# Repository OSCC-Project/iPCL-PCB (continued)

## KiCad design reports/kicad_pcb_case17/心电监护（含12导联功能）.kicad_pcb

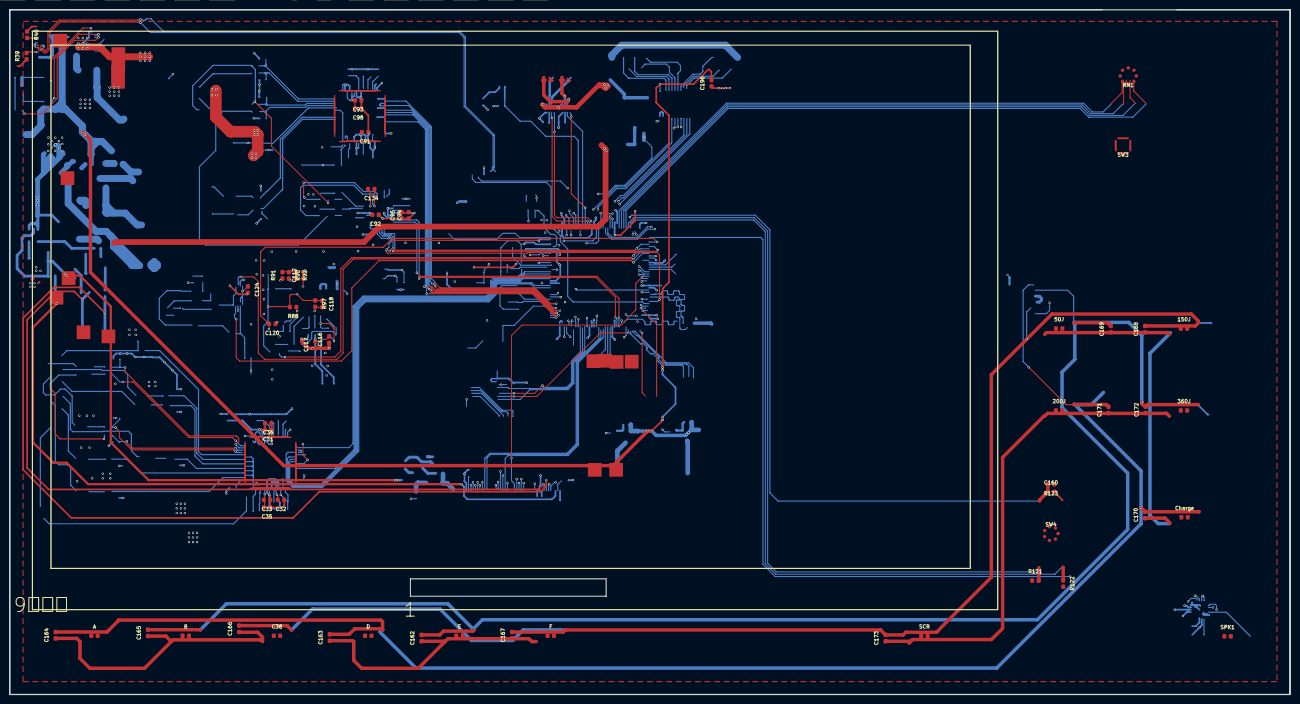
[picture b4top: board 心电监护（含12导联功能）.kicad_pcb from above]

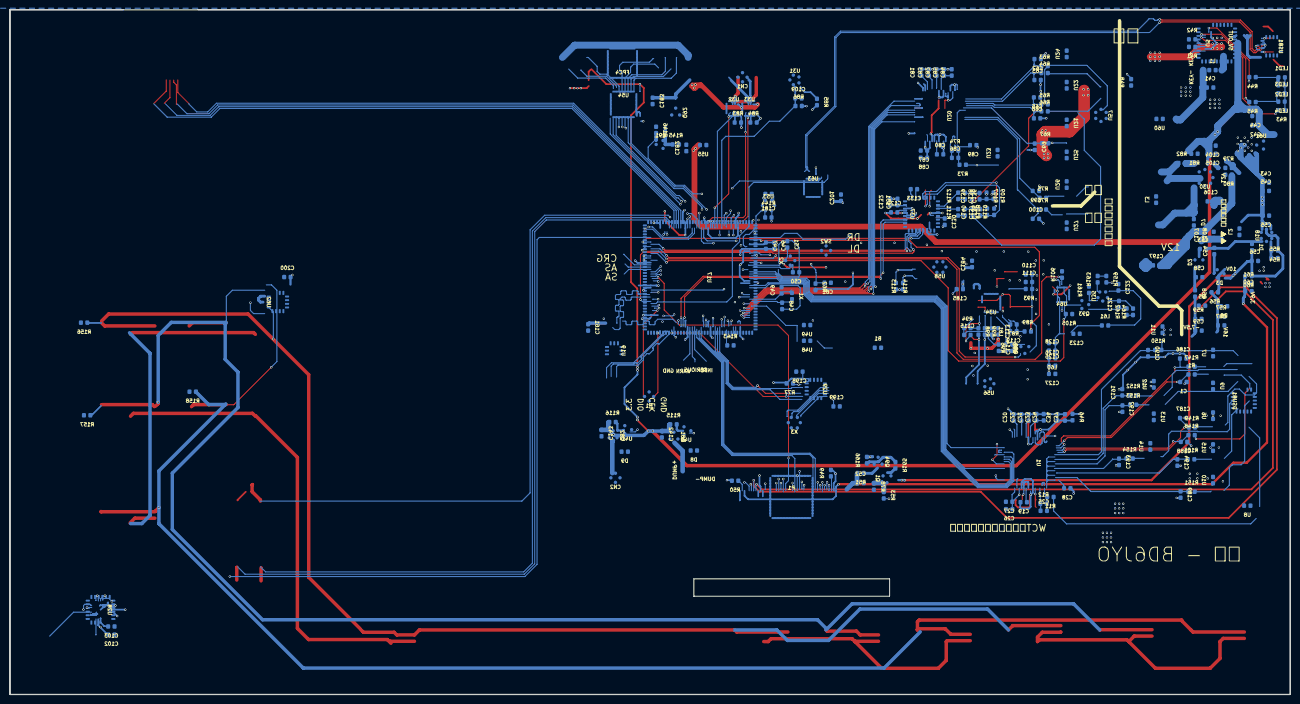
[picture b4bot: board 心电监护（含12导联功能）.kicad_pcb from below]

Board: 4 copper layers, 280.0 x 149.7 mm, 347 parts (289 on the bottom side), 274 nets.

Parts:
3.9V, 5V_OUT, 10V, 12V, 16V: test-point-0.5mm
50J, 150J, 200J, 360J: a5368f86a25146068be2408b3668e740
-7.5V: test-point-0.5mm
A: a5368f86a25146068be2408b3668e740
B: a5368f86a25146068be2408b3668e740
B1: 4e590728481542f894c6a4870e128ca6
C1, C19, C20, C21, C22, C23, C24, C25, C26, C27, C28, C31, C32, C33, C34, C35, C36, C37, C42, C43, C44, C45, C46, C47, C48, C49, C50, C51, C52, C53, C54, C55, C56, C57, C58, C59, C60, C61, C62, C63, C65, C66, C69, C80, C81, C82, C83, C84, C85, C86, C87, C88, C89, C91, C92, C93, C94, C95, C98, C99, C100, C102, C103, C104, C105, C106, C107, C108, C109, C110, C111, C112, C113, C114, C115, C116, C117, C118, C119, C120, C121, C122, C124, C125, C126, C127, C128, C129, C130, C131, C132, C133, C134, C135, C136, C137, C138, C139, C140, C142, C143, C160, C161, C162, C163, C164, C165, C166, C167, C168, C169, C170, C171, C172, C173, C181, C182, C183, C184, C185, C186, C187, C188, C189, C190, C191, C192, C193, C194, C196, C198, C199, C200, C201: b7945a7e5b5c4a0aa7293b7f08fbaef7
C38: a5368f86a25146068be2408b3668e740
C41: 0e92c3d665db49bfb035b3a293e8a128
C123: ba47d43f92bb44e8b675b656d21041e6
C197: 6b21cd17fdb1462b875b850f8c1df456
CN1: 31d9f30041aa4ccb86dff98b6131f5a0
CN2: b02f860fd06041c4a03dff9e4e9a9d56
Charge: a5368f86a25146068be2408b3668e740
D: a5368f86a25146068be2408b3668e740
D1: 4b7626d9e3dc4ab4b1f5a40703e7ad59
D2, D3: 9c46af5127664003a46938238bb95ce1
D5, D6: 91ac8cb66aa04e808b69908295fe52e9
D7: 4c0e46bca29c4c6b81e5bf8c40af5be7
D8, D9: 5d0c16af079e42cfb253586e56d88736
DSUB1: 39b3793dbb04477d8bb42acea19422e9
DUMP+: test-point-0.5mm
DUMP-: test-point-0.5mm
E: a5368f86a25146068be2408b3668e740
F: a5368f86a25146068be2408b3668e740
FPC4: cb7d1c6156c34550a72fbf6a566a445a
GND: test-point-0.5mm
H1: 73f75bc231734ab9b4af43c31c29b39a
INFO: test-point-0.5mm
KEY+: test-point-0.5mm
KEY-: test-point-0.5mm
L1, L2: 1c23e037bce9498e9d951e8e681f1670
L3: 7a41cdcb27974877a56d5e23ab1ec39c
L60, L61, L81: 870cf3ad3e8f4b4481cadf8c89e3570a
LED1, LED2: 8b6564fdb2984d8197e865d045b8fe55
LED3: 65519d43b7064742813920c87ef6d4bf
LED4: 598762258a40444a8d3e6d632ccb337f
P1: a40cf0907b584343b00a4ee89c43669f
Q1, Q94: 470d97b0775b4d198ab0a74007893075
Q80, Q91, Q93: 8f0cd7aa9b764cbb80294a6c3e96d042
Q81, Q82: 9c46af5127664003a46938238bb95ce1
Q92: 68f6e82e2aea405c86c92c228f40702a
R1, R11, R12, R39, R40, R41, R42, R43, R44, R45, R46, R48, R49, R50, R51, R53, R54, R55, R56, R57, R58, R59, R60, R61, R62, R63, R64, R65, R66, R67, R73, R74, R75, R76, R77, R78, R79, R80, R82, R83, R84, R85, R86, R107, R108, R109, R110, R111, R112, R115, R116, R121, R122, R123, R143, R144, R145, R146, R147, R148, R149, R150, R151, R152, R153, R154, R155, R156, R157, R158, R159, R161, R162, R163, R164, R165, R166: 6f4aec6b1ebd449284c4ed49b9f19c31
R81: 2640120e0c76485ea60f8241144970ee
R87, R88, R89, R90, R91, R92, R93, R94, R95, R96, R97, R98, R99, R105, R106, R113, R114: 72e69c7603aa4edf8d29985f96c3ffe3
RN1: f1a74709e41b44a49574d699140b981f
SCR: a5368f86a25146068be2408b3668e740
SERIOUS: test-point-0.5mm
SPK1: 1b99ed72e9ac48ff8cb342a8ca9438c6
SW2: d0581e74fb914419ae2671adb5a968e7
SW3: 61bb987df6594ec6aa08c5dfcf8cee7c
SW4: 5f2b1aeb4a7d44ef8f491db563029554
U1, U20: TQFP-64_L10.0-W10.0-P0.50-LS12.0-BL
U5: cda39a85f97f41da830f81e8102de607
U6, U7, U8, U9, U10, U11, U12, U13, U14, U15, U21, U22, U23, U24, U25, U26, U27: 3f067aeec7c64175b2af7de4432b0669
U17: 89ed9195d4da4ada9931ee24c9e82a56
U18: e26b29af5d3f47a2965616f8d64ee69f
U19: a692673a5b344db89108dd844333f42a
U28: 8c9603684b3541058d95c2816666bebf
U29: d974324436f24b31814a4f8fc4d5b4bf
U30: 13cf52a2d9d9472bb05fe23fd8a69656
U31: 0a26765eeea44677acb247cc684c720b
U32, U33: 6d84bfecd9c94e88953123fda0afa9f7
U34: c5b33378315045b09780d9a8558cf4a4
U35: 29113d248a374adb80ce29dd50db5bf2
U37: 27372514ed45449388039cdfe96d8606
U40, U41: 834b13ce004b4490974a88d7843f761e
U48, U49: 7f0149cf019141c4833b5e4a4083405b
U53: de513661803b4037b6dc43a570e5daf4
U54: 0a84c70d30504cdcbd1cdec5ae9f3825
U55: 878b8447bdf04bb5be66ff489c0c8653
U56: 182b4934e41a48109336b9ae788470fd
U57: 2ca98667745e4fdd9b327ad6b16e81a0
U58: e3607cc16cd8417c834685cb4e5d04ee
U60: 4159cb5bb8b246f8baa1c9276ab41b4d
U61: e27e0761c1574ba7a62473e696934099
U62: 1df479a9ca484c11abf2842f7ab43469
U63: dc02eda9a70e418f8f8ba1b589faf7b3
U64: 97c68005ac344068b28a0831b9720797
USB1: b8c1298db2324bd1a6e1152626922f4e
WARN: test-point-0.5mm
X1: 277eb1032c754119a9ed39082baf9071
X2: dfcdc5bc787d42879911d09280935ab4
X3: f82ad2619099490298d985a7bf518193

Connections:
3.3V: C26.2, C27.2, C43.2, C45.2, C55.1, C87.2, C88.2, C125.2, C127.1, C161.2, C184.2, C198.2, C199.2, C200.1, C201.2, H1.1, L2.2, L60.1, P1.12, P1.44, R46.2, R49.1, R50.1, R62.1, R77.1, R83.1, R84.1, R85.1, R86.1, R107.2, R108.1, R113.2, R114.1, R121.1, R122.2, R123.1, RN1.1, RN1.2, RN1.3, RN1.4, U1.48, U1.50, U1.52, U17.17, U17.30, U17.39, U17.52, U17.62, U17.72, U17.84, U17.95, U17.108, U17.121, U17.131, U17.143, U17.144, U18.4, U18.6, U19.8, U20.48, U20.50, U20.52, U28.4, U29.1, U29.9, U29.10, U32.8, U33.8, U37.14, U37.23, U49.2, U54.23, U54.24, U58.2, U61.2, U62.14, U63.4, U63.16
3V3SGM: C123.1, C124.1, C126.2, C128.1, L60.2, L61.2, U64.1, U64.2, U64.10
5V: U5.23, U5.24, USB1.2, USB1.11
5V_OUT: 5V_OUT.1, C42.2, C44.2, C102.1, C104.1, C105.1, C142.2, C143.2, C196.2, FPC4.9, Q81.2, Q82.2, R81.1, R115.2, R116.2, U5.19, U5.20, U5.21, U5.22, U28.17, U30.6, U54.1, U61.3
12V: 12V.1, C107.1, C108.1, C182.1, C197.1, D7.1, Q92.3, R80.2, R145.1, U55.1
12VP: C183.2, FPC4.1, FPC4.2, FPC4.3, FPC4.4, FPC4.26, FPC4.27, FPC4.28, Q92.2, U32.1, U33.1
$1N2542: C28.1, U1.1, U1.3, U1.5, U1.7, U1.9, U1.11, U1.64
$1N3912: C19.2, U1.55
$1N6305: C25.1, R11.1, R12.1, U1.62, U1.63
$2N198: R39.2, USB1.4
$2N200: R40.2, USB1.10
$2N826: R41.2, U5.6
$2N1088: R42.1, U5.5
$2N1140: L1.2, U5.14, U5.15, U5.16, U5.17, U5.18
$2N1172: C41.2, L1.1, U5.9, U60.2
$2N1635: LED1.1, LED2.2, LED3.1, LED4.2, R43.2
$2N1654: LED1.2, LED2.1, R44.2
$2N1670: LED3.2, LED4.1, R45.2
$2N4501: C53.1, C54.1, D1.2, L2.1, U18.1
$2N4625: C54.2, D3.3
$2N4652: C53.2, D2.3
$2N4895: D3.2, R56.2
$2N5230: C58.2, D2.1, R58.2
$2N9177: KEY+.1, U5.8
$2N10612: R79.2, R80.1, U30.5
$2N10742: R82.1, U30.8
$2N10757: L3.1, R81.2, R82.2, U30.7
$2N10979: D7.2, L3.2, U30.1
$2N18236: C106.2, U30.3
$3N2281: C49.2, U17.9, X1.2
$3N2284: C48.2, U17.8, X1.1
$3N2377: C50.1, U17.23, X2.3
$3N2471: C51.1, U17.24, X2.1
$3N4920: P1.43, R49.2
$3N4978: P1.4, R50.2
$3N8713: SPK1.1, U28.16
$3N8719: SPK1.2, U28.14
$3N9090: C103.1, U28.18
$3N10389: Q1.1, R53.2, R78.2
$3N12468: R83.2, U32.7
$3N12589: R84.2, U33.7
$3N19253: U17.6, U48.1, U49.1
$3N38319: R85.2, U31.1
$3N43045: R144.2, U53.3
$3N43809: Q91.3, Q92.1, R145.2
$3N86409: Q1.3, R165.1
$3N86567: Q94.1, R165.2, R166.2
$3N86579: Q94.3, R51.2
$4N2284: C89.1, U20.11, U20.64
$4N2324: C80.2, U20.55
$4N2370: C86.1, R73.1, R74.1, U20.62, U20.63
$4N6569: U34.13, U34.14
$4N6571: R93.1, U34.8
$4N6575: C112.1, R92.2, U34.10
$4N6576: R90.1, R91.2, R92.1
$4N6579: C113.2, L81.2, U34.4
$4N6582: C115.1, R94.1, R98.2, U34.2
$4N6583: C114.2, C115.2, R94.2, U34.1
$4N6584: C114.1, R95.1, R96.2
$4N6585: R95.2, U34.5
$4N6586: Q80.3, R96.1
$4N6596: C118.2, R97.2, R99.2, U34.3
$4N6599: C119.1, R87.1, R88.1, U34.6
$4N6602: C119.2, R87.2, R89.2, U34.7
$4N7474: R159.2, R163.1
$4N7475: C122.1, L61.1, U35.5
$4N7479: R162.2, R164.2
$4N7480: C121.1, R164.1, U35.4
$4N7481: C121.2, Q93.1, R162.1
$4N7483: Q93.3, U64.5, U64.7
$4N7496: R163.2, U35.1
$4N7497: Q93.2, R161.2, U35.3
$4N12574: C130.2, U37.27
$4N12606: C129.1, U37.11
$4N12858: C134.2, U37.1
$4N12860: C133.2, U37.7
$4N12864: C134.1, U37.2
$4N12868: C133.1, U37.8
$4N13059: C137.2, R108.2, R110.2, U37.3
$4N13071: C138.2, R107.1, R109.1, U37.4
$4N13252: C135.2, C137.1, C140.1
$4N13256: C136.2, C138.1, C139.1
$4N13314: C135.1, R111.2
$4N13340: C136.1, R112.2
$4N14062: Q81.1, R115.1, U40.3
$4N14471: Q82.1, R116.1, U41.3
$4N14495: D8.1, DUMP+.1, Q81.3
$4N14511: CN2.1, D9.1, Q82.3
$6N33304: U62.3, U62.4
A3.3: C31.2, C32.2, C33.2, C34.2, C35.2, C36.2, C37.2, C46.2, C47.2, C91.2, C92.2, C93.2, C94.2, C95.2, C98.2, C185.2, L81.1, R46.1, R90.2, R144.1, U1.19, U1.21, U1.22, U1.54, U1.56, U1.59, U17.33, U20.19, U20.21, U20.22, U20.54, U20.56, U20.59, U28.2, U37.12, U37.28, U37.29, U53.4, U58.1
ADC_REF3.3: C181.2, U17.32, U53.5, U53.6
AGND: C1.2, C19.1, C20.1, C21.1, C22.1, C23.1, C24.1, C28.2, C31.1, C32.1, C33.1, C34.1, C35.1, C36.1, C37.1, C46.1, C47.1, C62.2, C63.1, C65.2, C66.1, C69.1, C80.1, C81.1, C82.1, C83.1, C84.1, C85.1, C89.2, C91.1, C92.1, C93.1, C94.1, C95.1, C98.1, C99.2, C100.1, C129.2, C130.1, C131.1, C132.1, C181.1, C185.1, C186.1, C187.1, C188.2, C189.1, C190.1, C191.1, C192.1, C193.1, C194.1, R48.1, R109.2, R110.1, U1.17, U1.18, U1.20, U1.23, U1.25, U1.32, U1.53, U1.57, U1.58, U17.31, U20.17, U20.18, U20.20, U20.23, U20.25, U20.32, U20.53, U20.57, U20.58, U28.3, U37.10, U37.13, U53.1, U53.2
C1: DSUB1.12, R151.1, U10.2
C2: DSUB1.1, R150.1, U11.2
C3: DSUB1.2, R152.1, U12.2
C4: DSUB1.3, R153.1, U13.2
C5: DSUB1.4, R154.1, U14.2
C6: DSUB1.5, R155.1, U15.2
C_SA: R121.2, SW4.A, U17.67
C_SB: R122.1, SW4.B, U17.68
D+: U63.5, USB1.6, USB1.8
D-: U63.6, USB1.5, USB1.7
ECG_CLK: U1.40, U17.19
ECG_CS: U1.39, U17.18
ECG_MISO: U1.43, U17.20
ECG_MOSI: U1.34, U17.21
ECG_RESET: U1.35, U1.36, U17.14
ECG_START: U1.38, U17.15
FB: R54.1, R55.2, U18.3
GND: B1.1, C26.1, C27.1, C41.1, C42.1, C43.1, C44.1, C45.1, C48.1, C49.1, C50.2, C51.2, C52.1, C55.2, C56.1, C57.1, C58.1, C59.1, C60.1, C61.2, C87.1, C88.1, C102.2, C103.2, C104.2, C105.2, C106.1, C107.2, C108.2, C109.1, C110.2, C111.2, C112.2, C113.1, C116.1, C117.1, C120.1, C122.2, C123.2, C124.2, C125.1, C126.1, C127.2, C128.2, C142.1, C143.1, C160.2, C161.1, C182.2, C183.1, C184.1, C196.1, C197.2, C198.1, C199.1, C200.2, C201.1, CN2.2, CN2.3, CN2.4, D2.2, D5.1, D6.2, D8.2, D9.2, DSUB1.6, DSUB1.7, DSUB1.8, DSUB1.16, DSUB1.17, DUMP-.1, FPC4.11, FPC4.12, FPC4.13, FPC4.14, FPC4.15, FPC4.16, FPC4.17, FPC4.18, GND.1, H1.4, KEY-.1, P1.3, P1.11, P1.13, P1.15, P1.16, P1.17, P1.18, P1.24, P1.25, P1.32, P1.33, P1.34, P1.46, P1.47, P1.48, P1.51, P1.52, Q1.2, Q91.2, R39.1, R40.1, R41.1, R42.2, R48.2, R55.1, R57.1, R59.1, R61.1, R78.1, R79.1, R91.1, R105.2, R106.1, R143.1, R146.2, R156.1, R157.1, R158.1, R161.1, SW2.2, SW3.1, SW3.11, SW3.12, SW4.6, SW4.7, SW4.C, SW4.E, U1.31, U1.33, U1.37, U1.41, U1.49, U1.51, U5.7, U5.31, U5.33, U6.1, U7.1, U8.1, U9.1, U10.1, U11.1, U12.1, U13.1, U14.1, U15.1, U17.16, U17.38, U17.51, U17.61, U17.83, U17.94, U17.107, U17.120, U17.130, U18.2, U19.4, U19.9, U20.31, U20.33, U20.37, U20.41, U20.49, U20.51, U21.1, U22.1, U23.1, U24.1, U25.1, U26.1, U27.1, U28.5, U28.15, U28.21, U29.6, U29.7, U29.8, U30.2, U30.4, U31.3, U31.4, U31.5, U32.4, U32.9, U33.4, U33.9, U34.11, U34.12, U35.2, U37.17, U37.24, U40.2, U41.2, U54.2, U54.11, U54.12, U54.13, U54.22, U55.2, U56.5, U58.4, U60.1, U61.1, U62.7, U63.1, U64.6, USB1.1, USB1.12, USB1.13, USB1.14, X2.2, X2.4, X3.5, X3.6
I2S_SCK: U17.73, U28.9, U28.10
I2S_SD: U17.29, U28.7
I2S_WS: U17.115, U28.8
II+: C1.1, R1.2, U1.16
II-: C186.2, R147.2, U1.15
III+: C188.1, R148.2, U1.14
III-: C187.2, R149.2, U1.13
INFO: INFO.1, U17.124
KEYBOARD_IRQ: U17.44, U62.6
KEY_CFM: C160.1, R123.2, SW4.D, U17.60
L1: R44.1, U5.32
L2: R45.1, U5.1
L3: R43.1, U5.2
LA: DSUB1.10, R149.1, U6.2
LCD_3.9V: 3.9V.1, C60.2, P1.5, P1.45, R60.1, R61.2
LCD_10V: 10V.1, C56.2, D1.1, D3.1, P1.8, Q94.2, R54.2, R60.2, R166.1, U18.5
LCD_16V: 16V.1, C57.2, D6.1, P1.10, R56.1, R57.2
LCD_-7.5V: -7.5V.1, C59.2, D5.2, P1.9, R58.1, R59.2
LCD_CLK: P1.14, U17.92
LCD_LED: C52.2, P1.49, P1.50, R51.1
LCD_LEDCON: R53.1, U17.82
LCD_RST: P1.7, U17.81
LINE_ADCH2: 200J.2, A.2, C163.2, C164.2, C170.2, C171.2, Charge.2, D.2, R158.2, U17.57, U62.1
LINE_BE53: 50J.2, 360J.2, B.2, C162.2, C165.2, C169.2, C172.2, E.2, R157.2, U17.58, U62.2
LINE_CF1S: 150J.2, C38.2, C166.2, C167.2, C168.2, C173.2, F.2, R156.2, SCR.2, U17.59, U62.5
LL: DSUB1.11, R1.1, R148.1, U9.2
MC: R67.1, U25.2, U57.3
MCU_BOOT0: R143.2, U17.138
MCU_RESET: C61.1, R62.2, SW2.3, U17.25
MECG_CLK: U17.1, U20.40
MECG_CS: U17.3, U20.39
MECG_MISO: U17.4, U20.43
MECG_MOSI: U17.5, U20.34
MECG_RESET: U17.7, U20.35, U20.36
MECG_START: U17.2, U20.38
MII+: C62.1, R63.2, U20.16
MII-: C63.2, R64.2, U20.15
MIII+: C65.1, R65.2, U20.14
MIII-: C66.2, R66.2, U20.13
MLA: C140.2, R66.1, U21.2, U57.5
MLL: C139.2, R63.1, R65.1, U24.2, U57.4
MODE_12D: RN1.7, SW3.4, U17.65
MODE_CC: RN1.6, SW3.3, U17.64
MODE_JH: RN1.5, SW3.2, U17.63
MODE_SYS: RN1.8, SW3.5, U17.66
MRA: R64.1, U22.2, U57.6
MRL: R73.2, U23.2, U57.1
MRX: U17.102, U63.2
MTX: U17.110, U63.3
MV: C69.2, R67.2, U20.12
NAND_CLK: U17.113, U19.3
NAND_CMD: U17.116, U19.5
NAND_D0: U17.98, U19.6
NAND_D1: U17.99, U19.7
NAND_D2: U17.111, U19.1
NAND_D3: U17.112, U19.2
PD+: C116.2, R98.1, U56.1
PD-: C117.2, R99.1, U56.2
PDL+: C99.1, R75.2, U20.8
PDL-: C100.2, R76.2, U20.7
PDL_XD: R76.1, U27.2
PDL_XJ: R75.1, U26.2
PLRE_DUMP: U17.142, U40.1
PLRE_VLVE: U17.141, U41.1
PRINER_12V_CON: Q91.1, R146.1, U17.43
PRINT_CLK: U17.136, U54.20
PRINT_CLK_D: FPC4.23, U54.4
PRINT_DI1: U17.128, U54.14
PRINT_DI1_D: FPC4.5, U54.10
PRINT_DI2: U17.137, U54.21
PRINT_DI_D: FPC4.24, U54.3
PRINT_LAT: U17.90, U54.19
PRINT_LAT_D: FPC4.22, U54.5
PRINT_MA+: CN1.2, U32.2
PRINT_MA-: CN1.4, U32.3
PRINT_MB+: CN1.3, U33.2
PRINT_MB-: CN1.1, U33.3
PRINT_PAPER: C109.2, R86.2, U17.45, U31.2
PRINT_PHA: U17.47, U32.6
PRINT_PHB: U17.49, U33.6
PRINT_SIGA: U17.48, U32.5
PRINT_SIGB: U17.50, U33.5
PRINT_STB1: U17.89, U54.18
PRINT_STB1_D: FPC4.21, U54.6
PRINT_STB2: U17.88, U54.17
PRINT_STB2_D: FPC4.20, U54.7
PRINT_STB3: U17.132, U54.16
PRINT_STB3_D: FPC4.8, U54.8
PRINT_STB4: U17.129, U54.15
PRINT_STB4_D: FPC4.7, U54.9
RA: DSUB1.9, R147.1, U7.2
RD+: U56.3, U64.9
RD-: U56.4, U64.3
RECG_CLK: U17.101, U37.20
RECG_CS: U17.77, U37.18
RECG_MISO: U17.75, U37.21
RECG_MOSI: U17.76, U37.19
RECG_RESET: U17.119, U37.15
RECG_START: U17.118, U37.16
RESPN: R112.1, U37.32
RESPP: R111.1, U37.31
RGB_B3: P1.35, U17.126
RGB_B4: P1.36, U17.127
RGB_B5: P1.37, U17.37
RGB_B6: P1.38, U17.139
RGB_B7: P1.39, U17.140
RGB_DE: P1.42, U17.22
RGB_G2: P1.26, U17.42
RGB_G3: P1.27, U17.125
RGB_G4: P1.28, U17.69
RGB_G5: P1.29, U17.70
RGB_G6: P1.30, U17.97
RGB_G7: P1.31, U17.117
RGB_HSYNC: P1.40, U17.96
RGB_R3: P1.19, U17.46
RGB_R4: P1.20, U17.103
RGB_R5: P1.21, U17.104
RGB_R6: P1.22, U17.100
RGB_R7: P1.23, U17.91
RGB_VSYNC: P1.41, U17.40
RL: DSUB1.14, R11.2, U8.2
RLDINV: C25.2, R12.2, U1.61
RLDINVM: C86.2, R74.2, U20.61
ROW_23S: 200J.1, 360J.1, C171.1, C172.1, C173.1, SCR.1, U17.56
ROW_ABC: A.1, B.1, C38.1, C164.1, C165.1, C166.1, U17.53
ROW_C51: 50J.1, 150J.1, C168.1, C169.1, C170.1, Charge.1, U17.55
ROW_DEF: C162.1, C163.1, C167.1, D.1, E.1, F.1, U17.54
SCL: R113.1, U17.11, U28.11, U58.6
SDA: R114.2, U17.10, U28.12, U58.5
SERIOUS: SERIOUS.1, U17.123
SPO2_CAP: Q80.1, U17.78
SPO2_DA1: R159.1, U17.41
SPO2_IR_CS: R105.1, U17.80, U64.4
SPO2_RED_CS: R106.2, U17.79, U64.8
SPO2_VSIG: C120.2, R89.1, U17.35
SWD_CLK: H1.3, U17.109
SWD_DIO: H1.2, U17.105
TOUCH_CLK: U17.133, U29.16
TOUCH_CS: U17.114, U29.15
TOUCH_DIN: U17.135, U29.14
TOUCH_DOUT: U17.134, U29.12
TOUCH_IRQ: R77.2, U17.27, U29.11
V1: C189.2, R151.2, U1.2
V2: C190.2, R150.2, U1.12
V3: C191.2, R152.2, U1.10
V4: C192.2, R153.2, U1.8
V5: C193.2, R154.2, U1.6
V6: C194.2, R155.2, U1.4
VCAP1: C22.2, U1.28
VCAP1M: C83.2, U20.28
VCAP2: C20.2, U1.30
VCAP2M: C81.2, U20.30
VCAP4: C21.2, U1.26
VCAP4M: C82.2, U20.26
VREF: C110.1, C111.1, C118.1, Q80.2, R88.2, R93.2, R97.1, U34.9
VREFP: C23.2, C24.2, U1.24
VREFPM: C84.2, C85.2, U20.24
VREFPR: C131.2, C132.2, U37.9
VRTC: B1.2, U48.2
WARN: U17.122, WARN.1
X1: U29.2, X3.4
X2: U29.4, X3.2
Y1: U29.3, X3.3
Y2: U29.5, X3.1

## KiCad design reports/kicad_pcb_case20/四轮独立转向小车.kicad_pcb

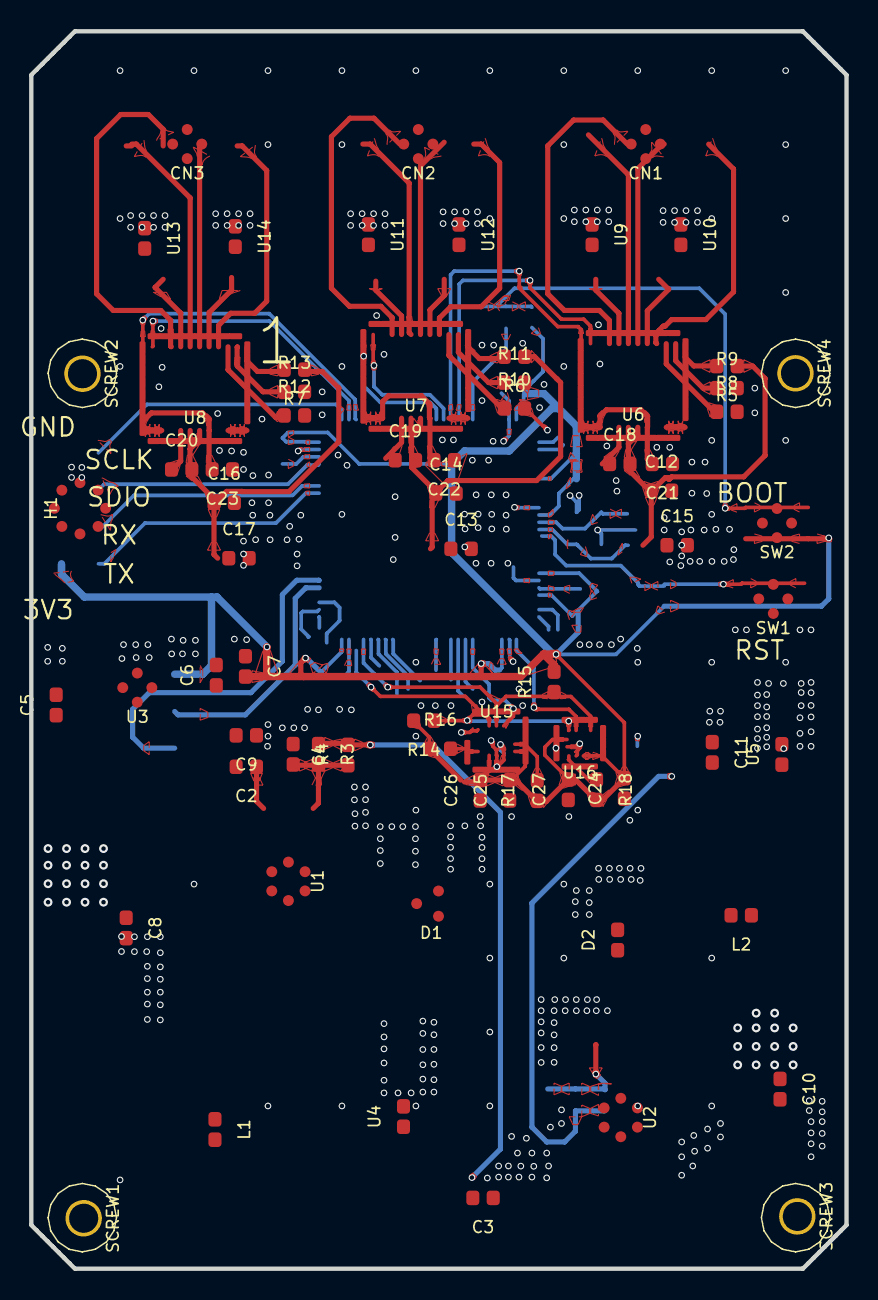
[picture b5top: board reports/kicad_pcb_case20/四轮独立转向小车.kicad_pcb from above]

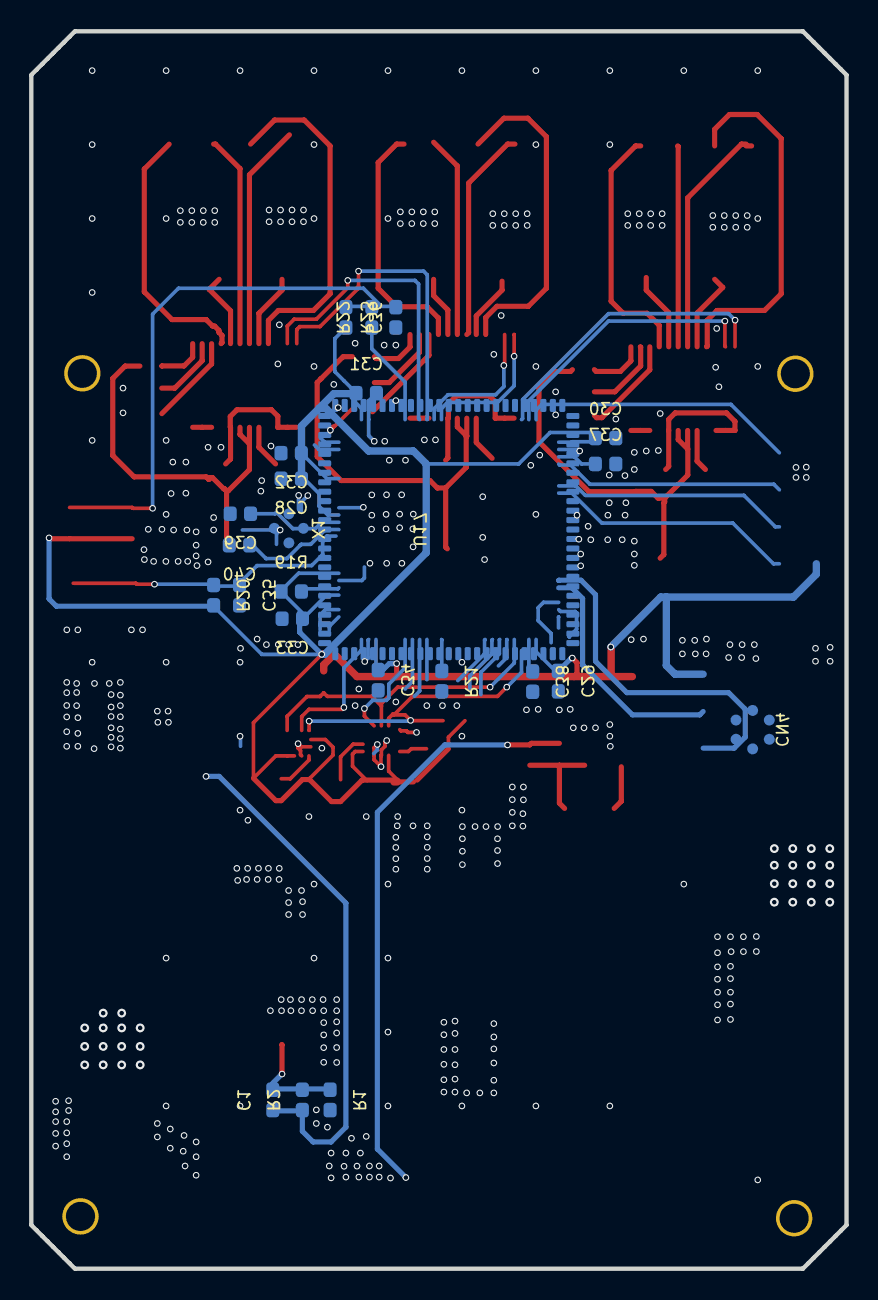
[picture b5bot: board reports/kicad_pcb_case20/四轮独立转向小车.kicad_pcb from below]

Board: 4 copper layers, 56.0 x 85.0 mm, 96 parts (24 on the bottom side), 74 nets.

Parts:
C1, C2, C3, C4, C7, C9, C11, C12, C14, C16, C18, C19, C20, C21, C22, C23, C24, C25, C26, C27, C28, C29, C30, C31, C32, C33, C34, C35, C36, C37, C38, C39, C40: 741784fa20ad4beab9dd8b8cbce97607
C5, C6: aff1c91bf3bd4904ada184bcb63bd701
C8: 7a3832be4b354b98872e54d8c51d8fc0
C10: d6d4783f7f544880a0d21885e087867f
C13, C15, C17: ec9f7c77078a4cf2bf6758d7ab16d38b
CN1, CN2, CN3: dd865c5c9bd54159bf1babbc1d1a2d46
CN4: a37b095bfeb148db8b87bdfda393230c
D1: 859d54e1422c4d42ac3895e3f528ce6d
D2: a0796d4780ca4c85b7bd60724495ac44
H1: 648849d55ce94beca6d893b0b88daeda
L1: 3b3ad4aecceb425685e8b86d0da21492
L2: 55714616dbcc47618b03be4d3a59a424
R1: 446156e8ca504404ab86e8dd60b77f34
R2, R3, R4, R5, R6, R7, R8, R9, R10, R11, R12, R13, R14, R15, R16, R17, R18, R19, R20, R21, R22, R23: 1996b2fb973e40a184d52a2e5e193df3
SCREW1, SCREW2, SCREW3, SCREW4: M2螺丝
SW1, SW2: f78937a3961e46c7aa83ae3777a1ced1
U1, U2: 8cce636d079c4c11b4736c07b0145fc3
U3: eb6f0a55a64841b28a24ff6840c76e95
U4: 1328727041374082a97455d8a57d9113
U5: 4ad9e22dd83d47c1b38c3bfc9eb01c2a
U6, U7, U8: bfbe2d57b84345cabb8ccf797da810bc
U9, U10, U11, U12, U13, U14: c9e3b9e131d747428ff4d6c03086196a
U15: 9212da6725b641f1870fb3cf18556f1c
U16: a1272321b06a4e088013c99c4785c5c8
U17: ac645093d34d4da5947e929ac4406eff
X1: 028e88c81bcf4cf5a4c76024a7a6c317

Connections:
3V3: C6.1, C7.2, C24.2, C25.2, C26.2, C27.2, C28.2, C29.2, C30.2, C31.2, C32.2, C33.2, C34.2, C36.1, CN4.4, H1.2, R14.2, R15.2, R16.1, R17.1, R18.2, R19.2, R20.1, SW2.1, SW2.2, U3.2, U3.4, U15.5, U15.8, U16.5, U16.9, U16.10, U17.6, U17.11, U17.19, U17.22, U17.28, U17.50, U17.75, U17.100
5V: C3.2, C4.2, L1.2, R3.1, U4.1
$1N385: R8.1, U6.3
$1N390: R9.1, U6.2
$1N1102: R5.2, U6.1
$1N1297: C18.1, U6.17
$1N1650: CN1.1, U6.4
$1N1657: CN1.2, U6.6
$1N1661: CN1.4, U6.7
$1N1666: CN1.3, U6.9
$1N1855: U6.22, U6.23, U6.24
$1N1980: U6.5, U10.2
$1N1985: U6.8, U9.2
$1N5748: D2.1, L2.1, U2.2
$1N5794: C1.1, R1.2, R2.1, U2.4
$1N7478: CN2.2, U7.6
$1N7484: CN2.1, U7.4
$1N7486: U7.5, U12.2
$1N7487: U7.8, U11.2
$1N7488: U7.22, U7.23, U7.24
$1N7495: R11.1, U7.2
$1N7496: R10.1, U7.3
$1N7500: C19.1, U7.17
$1N7516: R6.2, U7.1
$1N9481: C2.1, U1.4
$1N9513: D1.2, L1.1, U1.3, U1.6
$1N9581: C4.1, R3.2, R4.2, U1.2
$1N11006: R16.2, U15.4
$1N11076: R17.2, U15.9
$1N11426: R18.1, U16.7
$1N12744: C20.1, U8.17
$1N12752: U8.5, U14.2
$1N12754: U8.8, U13.2
$1N12757: CN3.1, U8.4
$1N12758: CN3.2, U8.6
$1N12760: R13.1, U8.2
$1N12762: R12.1, U8.3
$1N12764: U8.22, U8.23, U8.24
$1N12767: R7.2, U8.1
$1N18973: CN2.4, U7.7
$1N18978: CN2.3, U7.9
$1N23216: CN3.4, U8.7
$1N23226: CN3.3, U8.9
$2N1885: R21.2, U17.37
$2N1889: C37.2, U17.73
$2N1892: C38.2, U17.49
$2N1935: C36.2, R22.1, R23.1, SW2.3, SW2.4
$2N1987: R19.1, U17.21
BOOT0: R22.2, U17.94
CS1: U15.12, U17.32
CS2: U16.3, U17.26
DIR1: U8.12, U17.78
DIR2: U7.12, U17.89
DIR3: U6.12, U17.91
GND: C3.1, C5.2, C6.2, C7.1, C8.2, C9.1, C10.2, C11.1, C12.2, C13.2, C14.2, C15.2, C16.2, C17.2, C21.1, C22.1, C23.1, C24.1, C25.1, C26.1, C27.1, C28.1, C29.1, C30.1, C31.1, C32.1, C33.1, C34.1, C35.1, C37.1, C38.1, C39.1, C40.1, CN4.1, D1.1, D1.3, D2.2, H1.6, H1.8, R1.1, R4.1, R8.2, R9.2, R10.2, R11.2, R12.2, R13.2, R21.1, R23.2, SW1.1, SW1.2, U1.1, U2.3, U2.5, U2.6, U3.1, U4.2, U5.2, U6.10, U6.21, U6.25, U6.e30, U6.e31, U6.e32, U6.e33, U6.e34, U6.e35, U7.10, U7.21, U7.25, U7.e30, U7.e31, U7.e32, U7.e33, U7.e34, U7.e35, U8.10, U8.21, U8.25, U8.e30, U8.e31, U8.e32, U8.e33, U8.e34, U8.e35, U9.1, U10.1, U11.1, U12.1, U13.1, U14.1, U15.1, U15.6, U15.7, U16.6, U16.8, U17.10, U17.20, U17.27, U17.74, U17.99, X1.2, X1.4
NRST: C35.2, R20.2, SW1.3, SW1.4, U17.14
OSC_IN: C39.2, U17.12, X1.3
OSC_OUT: C40.2, U17.13, X1.1
SCL: R15.1, U15.13, U16.1, U17.47
SDA: R14.1, U15.14, U16.4, U17.48
STEP1: U8.11, U17.77
STEP2: U7.11, U17.90
STEP3: U6.11, U17.92
SWCLK: H1.7, U17.76
SWDIO: H1.5, U17.72
USART1_RX: H1.3, U17.69
USART1_TX: H1.1, U17.68
USART2_RX: CN4.2, U17.56
USART2_TX: CN4.3, U17.55
VIN: C2.2, C5.1, C8.1, C9.2, C10.1, U1.5, U2.1, U3.3
VINT1: C21.2, U6.13, U6.14, U6.15, U6.20
VINT2: C22.2, U7.13, U7.14, U7.15, U7.20
VINT3: C23.2, U8.13, U8.14, U8.15, U8.20
VM: C1.2, C11.2, C12.1, C13.1, C14.1, C15.1, C16.1, C17.1, C18.2, C19.2, C20.2, L2.2, R2.2, R5.1, R6.1, R7.1, U5.1, U6.18, U6.19, U7.18, U7.19, U8.18, U8.19

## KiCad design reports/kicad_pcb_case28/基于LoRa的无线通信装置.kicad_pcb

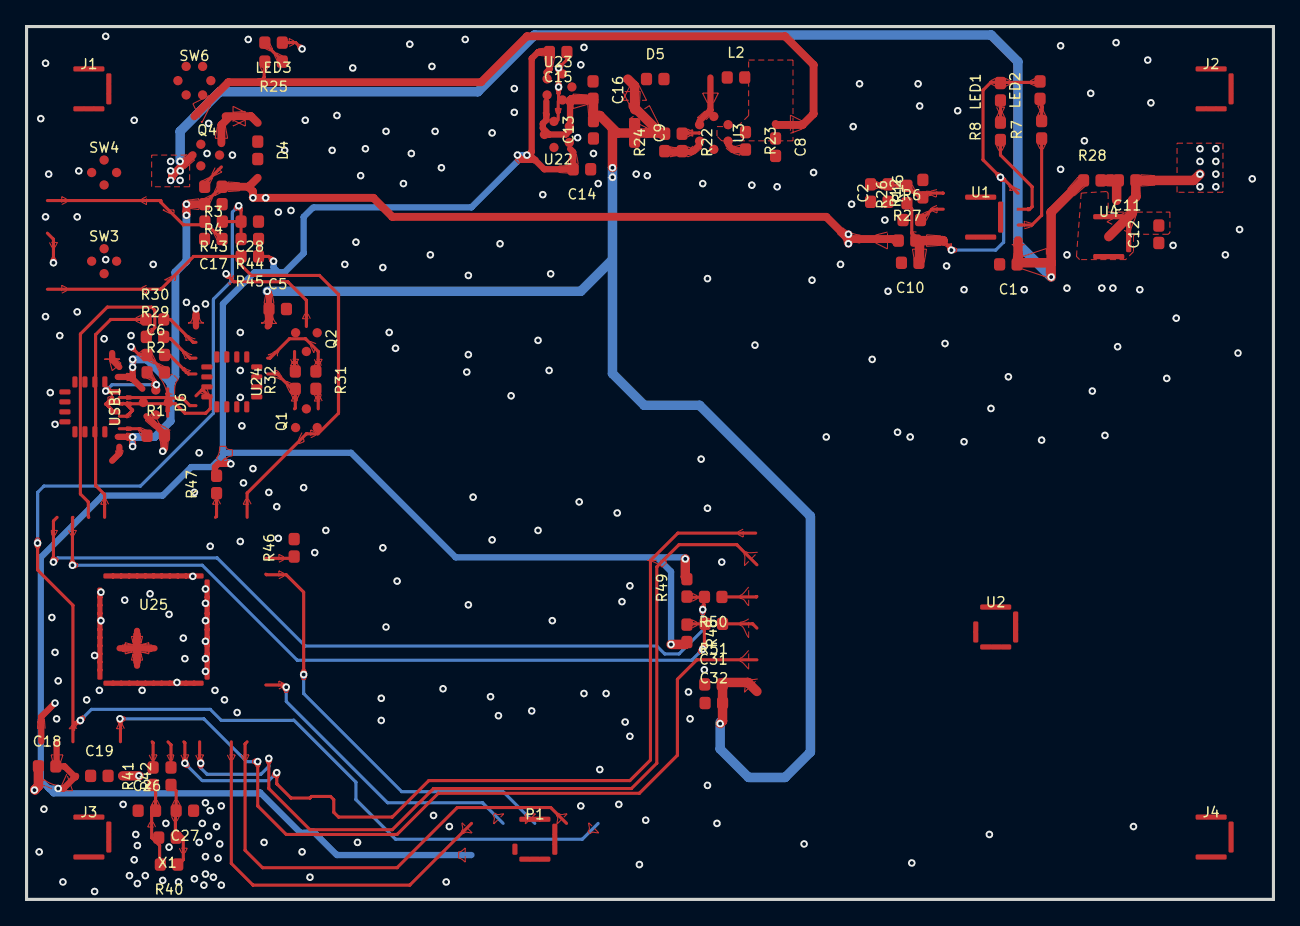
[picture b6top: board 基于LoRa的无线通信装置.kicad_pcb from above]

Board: 4 copper layers, 100.0 x 70.0 mm, 82 parts (1 on the bottom side), 54 nets.

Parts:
BT1: 729b0538b1a341618bd7cb661a22037e
C1, C2, C5, C6, C10, C11, C12, C13, C14, C15, C16, C17, C18, C26, C27, C28, C31, C32: 728c3cd86cf04df8a22e1e4cc7999c51
C8, C9, C19: 0ef207b2ddc3414e83e7b054e1746563
D4, D5: 676d0447cd86424a896932ccff1bae7a
D6: e0c8ee3166774c618a11b20e8e222c92
J1, J2, J3, J4: 80dfbe45b68b481aa7105046715aaf00
L2: 2034167f0bf242a3a26a8dc3db1fc2e8
LED1, LED2, LED3: 200a45bc1c5b4ae49fe0ed9de30a2fd3
P1: 05bcee1ffdeb4818b657f380baff9792
Q1, Q2: f84bb50dc16b4eebbbc153a766d294ee
Q4: 8c2e8aa9d77e42d396f854abff3bb53c
R1, R2, R3, R4, R6, R7, R8, R12, R22, R23, R24, R25, R26, R28, R29, R30, R31, R32, R40, R41, R42, R43, R44, R45, R46, R47, R48, R49, R50, R51: 4b5d1da49d5f414f8d7e734fdc2c3d13
R16: ac70bb08b9af453f8ca21aea1f141e78
R27: ec4374d47b594b4c8e782ae569b52ae8
SW3, SW4: 1dd01330da1848cb9c2ffa2976ee0adc
SW6: 2632c4b855ec4d98b8311925230dc043
U1: 3935d73832a2416f9a5aebe5287f6542
U2: dcc06a9b73524a81aeee7ab2401cb1f6
U3: 2284c91879ba47bc9110a7e60bbaa546
U4: c66c3a85e90e401798b81a6f34df2c7d
U22, U23: 66bfa27d5e4b46d190c30951e9c722a1
U24: 7085ec3b2db1445183ca8687b667aaa9
U25: 8a03bc13c8ea47d9bc086eef6bfe8dc9
USB1: 7392720445d54efebcca1ce4cbc0a62f
X1: 2ae6ab825c05453b879688213872a07e

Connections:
32K_NP: C27.2, R40.1, R42.1, X1.1
32K_XP: C26.2, R40.2, R41.1, X1.2
433RXD: R49.1, R50.2, U25.37
433TXD: R48.1, R51.2, U25.36
$1N2249: R1.1, USB1.B5
$1N2250: R2.1, USB1.A5
$1N2251: Q4.1, R3.2
$1N2259: R22.2, R24.1, U3.3
$1N2262: D5.2, L2.1, U3.1
$1N2264: R23.2, U3.4
$1N2265: LED3.2, R25.1
$1N2268: R6.2, U1.2
$1N2271: R8.1, U1.7
$1N2272: LED2.1, R7.2
$1N2273: C10.1, LED1.2, LED2.2, R26.1, R27.2, U1.4, U1.8
$1N2276: R7.1, U1.6
$1N2279: LED1.1, R8.2
$1N2281: C2.2, R12.1, R16.1, R26.2, U1.1
$1N2285: C11.2, R28.2, U4.6
$1N2300: D4.1, Q4.2, SW6.6
$1N2967: Q2.1, R32.2
$1N2968: Q1.1, R31.2
$1N2976: C6.2, U24.4
$1N2979: R29.2, U24.3
$1N2980: R30.2, U24.2
$1N2982: Q1.2, R32.1, U24.13
$1N2983: Q2.2, R31.1, U24.14
$1N4180: R41.2, U25.8
$1N4212: R42.2, U25.9
$1N4668: C17.1, R43.2, SW4.3, SW4.4
$1N4760: R47.1, U25.27
$1N4913: R46.1, U25.24
$1N7932: R50.1, U2.3
$1N7936: R51.1, U2.4
+3.3V: C14.2, C15.2, C18.2, C19.1, P1.1, R44.1, R45.1, R47.2, R48.2, R49.2, U22.5, U23.5, U25.2
+5V: C5.1, C9.1, C13.2, C16.2, C31.2, C32.2, D5.1, R24.2, U2.6, U22.1, U22.3, U23.1, U23.3, U24.16
AUX: U2.5, U25.6
CH340RXD: R29.1, U25.35
CH340TXD: R30.1, U25.34
EN: C28.2, P1.10, Q2.3, R43.1, R44.2, U25.3
GND: C1.2, C2.1, C5.2, C6.1, C8.2, C9.2, C10.2, C12.1, C13.1, C14.1, C15.1, C16.1, C17.2, C18.1, C19.2, C26.1, C27.1, C28.1, C31.1, C32.1, D6.1, LED3.1, P1.3, P1.5, P1.9, R1.2, R2.2, R4.1, R6.1, R12.2, R16.2, R22.1, R46.2, SW3.1, SW3.2, SW4.1, SW4.2, U1.3, U1.9, U2.7, U3.2, U4.2, U4.3, U4.4, U22.2, U23.2, U24.1, U25.1, U25.15, U25.38, U25.39, USB1.1, USB1.2, USB1.3, USB1.4, USB1.A1B12, USB1.B1A12
IO0: Q1.3, R45.2, SW3.3, SW3.4, U25.25
IO12_TDI: P1.8, U25.14
IO13_TCK: P1.4, U25.16
IO14_TMS: P1.2, U25.13
IO15_TDO: P1.6, U25.23
M0: U2.1, U25.10
M1: U2.2, U25.11
USBD+: D6.2, U24.5, USB1.A6, USB1.B6
USBD-: D6.3, U24.6, USB1.A7, USB1.B7
VBAT+: BT1.2, C1.1, Q4.3, R28.1, U1.5
VBAT-: BT1.1, C11.1, C12.2, U4.5, U4.7, U4.8, U4.9
VIN: C8.1, L2.2, R23.1, R25.2, SW6.5, U3.5
VUSB: D4.2, D6.4, R3.1, R4.2, R27.1, USB1.A4B9, USB1.B4A9

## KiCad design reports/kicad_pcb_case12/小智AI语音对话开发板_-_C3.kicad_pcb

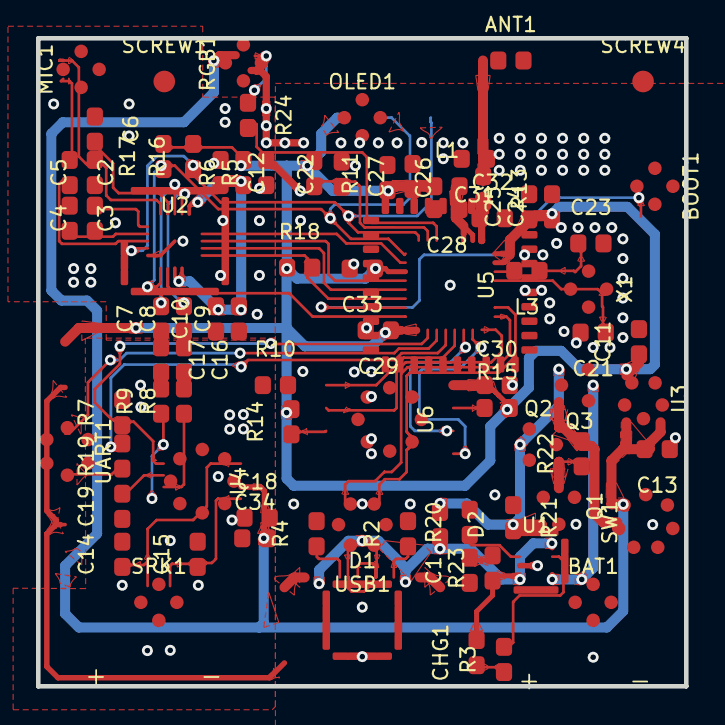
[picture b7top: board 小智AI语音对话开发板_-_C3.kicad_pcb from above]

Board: 4 copper layers, 36.0 x 36.0 mm, 82 parts (0 on the bottom side), 65 nets.

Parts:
ANT1: 114122dcd07c475ebe40200aac76a093
BAT1: 836278af07de4edf9717d25b6ec65016
BOOT1: b3649e5cefb54f17903855245019f32a
C1, C11, C13, C21, C23, C26, C34: 05a7991f1fa1490d8ece4ac6b500d086
C2, C3, C4, C5, C6, C7, C8, C9, C10, C12, C14, C15, C16, C17, C18, C19, C22, C24, C25, C27, C28, C29, C30, C31, C32, C33: 0ec62e40828d4649aa19c65134dcb0f5
CHG1: 3863a6ce95bc411989e1282ae348fc22
D1: f8ff3a072edc41319181636897a8a1f5
D2: b8e8c18369e049b7b784d5f799b39940
L1: 03394a9e29844b04822005f3f100cdb5
L3: 74fb0f8e922542549bbf8588ec507ccb
MIC1: 8ee6189173c347bc8e70b77e870f6d5d
OLED1: a6edf34580c248ed80574da6edd8c325
Q1: fe135372421846129297c4735aa2fbbf
Q2, Q3: 98a6dc606e334f6aaebd60298df2d4b0
R2, R3, R4, R5, R6, R7, R8, R9, R10, R11, R13, R14, R15, R16, R17, R18, R19, R20, R21, R22, R23, R24: 625c84422b324783a92dfa608e7f2de8
RGB1: f454c511d7fe482db86f9c1289e79ec1
SCREW1: e69
SCREW4: e70
SPK1: 836278af07de4edf9717d25b6ec65016
SW1: ef9e1cfde34a434b98abd3df30ee1c51
U1: 2e9ba12a0f1941e2b7ac0ab997b73013
U2: b9ed25adae7247a4a615f87e0d6ab6b0
U3: be9e5f7a6f904d7186a41fd7c1ac8e81
U4: db83f0b44aab47c98d8228258cb0e0b4
U5: 94ebbbc58b5d4ce1b5e713e5698fcb59
U6: d56c3286f2a54943b777986e50464eac
UART1: 4f676e4b75344455a55b32ce6fd398dd
USB1: 16bae89f927a4bc4a42fc9950053189a
X1: 1ae716d6e94945b49937000d937cc2f3

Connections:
3V3: C11.1, C24.1, C25.1, C26.2, C27.1, C29.1, C30.1, C33.1, L1.1, OLED1.2, R6.2, R11.1, R14.2, R15.2, R16.2, R17.2, R18.1, U3.5, U5.11, U5.17, U5.31, U5.32, U6.8, UART1.1
$1N629: R2.1, USB1.10
$1N642: R4.1, USB1.4
$1N2096: ANT1.1, C31.1, R13.1
$1N2098: C32.1, R13.2, U5.1
$1N2123: C28.1, L1.2, U5.2, U5.3
$1N2158: C21.1, U5.29, X1.3
$1N2350: R14.1, U6.3
$1N2553: R15.1, U6.7
$1N5759: C8.2, U2.12
$1N5760: C7.2, U2.13
$1N5772: C6.2, U2.14
$1N5774: C4.2, U2.16
$1N5775: C3.2, U2.17
$1N5776: C2.2, U2.18
$1N6630: R8.1, U4.3
$1N6631: R9.1, U4.4
$1N6634: C19.2, U4.2
$1N6639: C16.2, R8.2
$1N6640: C17.2, R9.2
$1N6885: R19.1, UART1.4
$1N19600: CHG1.1, R3.1
$1N19641: R3.2, U1.7
$1N26968: C2.1, MIC1.1
$1N27561: C15.1, SPK1.2, U4.5
$1N29918: C14.1, SPK1.1, U4.8
$1N30665: R20.1, U1.2
$1N42663: L3.2, U5.30
$1N42668: C23.1, L3.1, X1.1
$1N47594: D2.1, Q1.1, Q2.3, Q3.1, R21.2
$1N47654: Q1.3, Q2.1, R22.1
$1N52868: C1.2, R23.2
$1N55724: R24.1, RGB1.4
AU_3V3: C9.2, C10.2, C12.2, R6.1, U2.3, U2.4, U2.11
AU_GND: C3.1, C4.1, C5.1, C6.1, C9.1, C10.1, C12.1, MIC1.2, MIC1.3, R5.1, U2.5, U2.10, U2.20, U2.21
BAT+: BAT1.1, Q3.3, U1.5
BOOT: BOOT1.4, U5.15
CHIP_EN: C22.1, R11.2, U5.7
GND: BAT1.2, BOOT1.3, C1.1, C11.2, C13.1, C21.2, C22.2, C23.2, C24.2, C25.2, C26.1, C27.2, C28.2, C29.2, C30.2, C31.2, C32.2, C33.2, D1.2, OLED1.1, Q1.2, R2.2, R4.2, R5.2, R10.2, R20.2, R21.1, RGB1.3, U1.3, U1.9, U3.2, U5.33, U5.e114, U5.e115, U5.e116, U5.e117, U6.4, UART1.2, UART1.5, USB1.1, USB1.12, USB1.13, USB1.14, X1.2, X1.4
I2C_SCL: OLED1.3, R17.1, U2.1, U5.9
I2C_SDA: OLED1.4, R16.1, U2.19, U5.8
I2S_BCK: R18.2, U2.6, U5.14
I2S_DI: U2.7, U5.13
I2S_DO: U2.9, U5.10
I2S_MCK: U2.2, U5.16
I2S_WS: U2.8, U5.12
PA_EN: R7.1, U4.1, U5.18
PA_GND: C14.2, C15.2, C18.1, C19.1, C34.1, R7.2, R10.1, U4.7
PA_IN+: C8.1, C16.1
PA_IN-: C7.1, C17.1
SPI_CLK: U5.22, U6.6
SPI_CS0: U5.21, U6.1
SPI_ID: U5.23, U6.5
SPI_IQ: U5.24, U6.2
U1RXD: U5.19, UART1.3
U1TXD: R19.2, U5.20
USB_DN: D1.3, U5.25
USB_DN_IN: D1.4, USB1.5, USB1.7
USB_DP: D1.1, U5.26
USB_DP_IN: D1.6, USB1.6, USB1.8
VBUS: CHG1.2, D1.5, D2.2, R23.1, U1.4, U1.8, USB1.2, USB1.11
VMIC: C5.2, MIC1.4, U2.15
VOUT: Q2.2, Q3.2, R22.2, SW1.2
VSYS: C13.2, C18.2, C34.2, RGB1.2, SW1.3, U3.1, U3.3, U4.6, UART1.6
WS2812: R24.2, U5.6
